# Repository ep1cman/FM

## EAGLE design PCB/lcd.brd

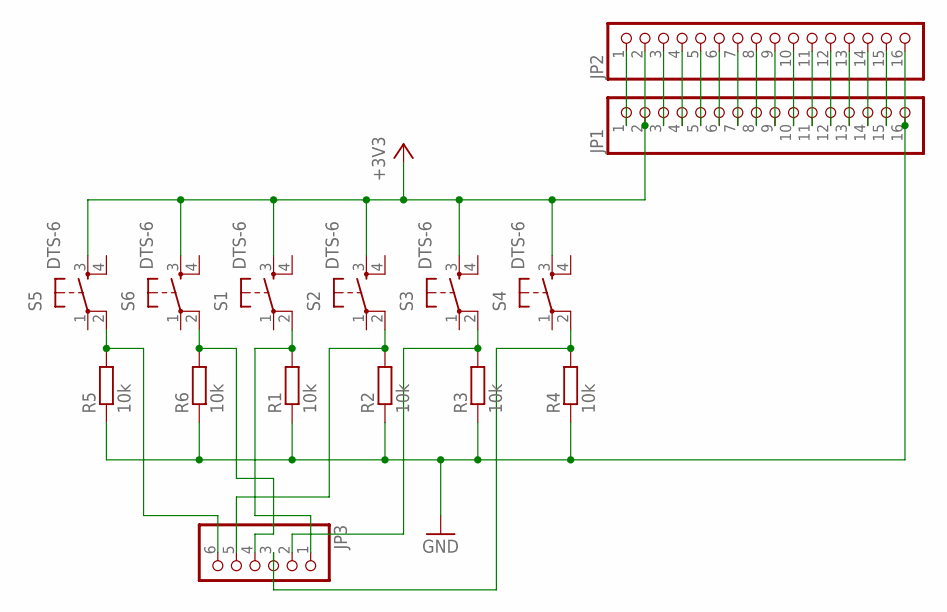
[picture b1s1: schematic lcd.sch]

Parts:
JP1, JP2: PINHD-1X16; 1X16
JP3: PINHD-1X6; 1X06
R1, R2, R3, R4, R5, R6: 10k; R0805
S1, S2, S3, S4, S5, S6: DTS-6

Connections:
+3V3: JP1.2, JP2.2, S1.3, S2.3, S3.3, S4.3, S5.3, S6.3
GND: JP1.16, JP2.16, R1.1, R2.1, R3.1, R4.1, R5.1, R6.1
unnamed: JP3.1, R1.2, S1.2
unnamed: JP3.5, R2.2, S2.2
unnamed: JP3.2, R3.2, S3.2
unnamed: JP1.1, JP2.1
unnamed: JP3.3, R4.2, S4.2
unnamed: JP3.6, R5.2, S5.2
unnamed: JP3.4, R6.2, S6.2
unnamed: JP1.3, JP2.3
unnamed: JP1.4, JP2.4
unnamed: JP1.5, JP2.5
unnamed: JP1.6, JP2.6
unnamed: JP1.7, JP2.7
unnamed: JP1.8, JP2.8
unnamed: JP1.9, JP2.9
unnamed: JP1.10, JP2.10
unnamed: JP1.11, JP2.11
unnamed: JP1.12, JP2.12
unnamed: JP1.13, JP2.13
unnamed: JP1.14, JP2.14
unnamed: JP1.15, JP2.15

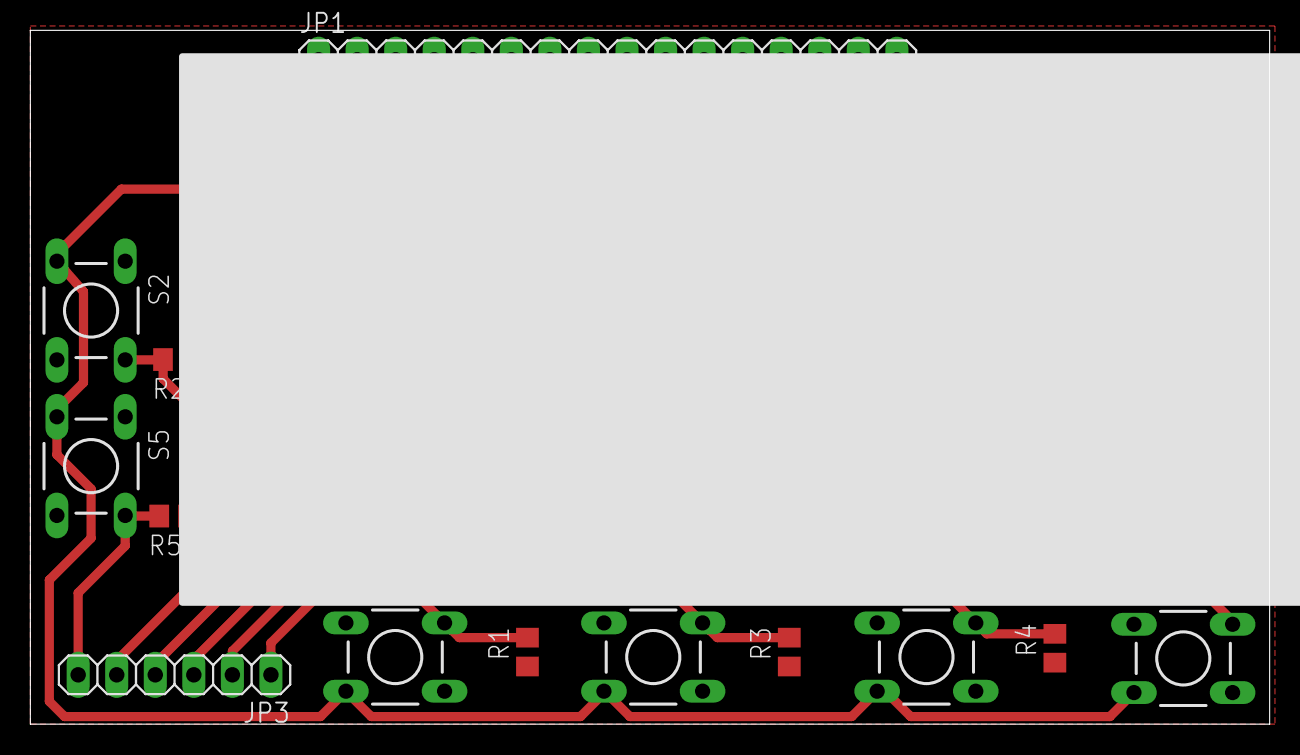
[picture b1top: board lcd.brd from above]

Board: 2 copper layers, 81.7 x 45.7 mm, 15 parts (0 on the bottom side), 22 nets.

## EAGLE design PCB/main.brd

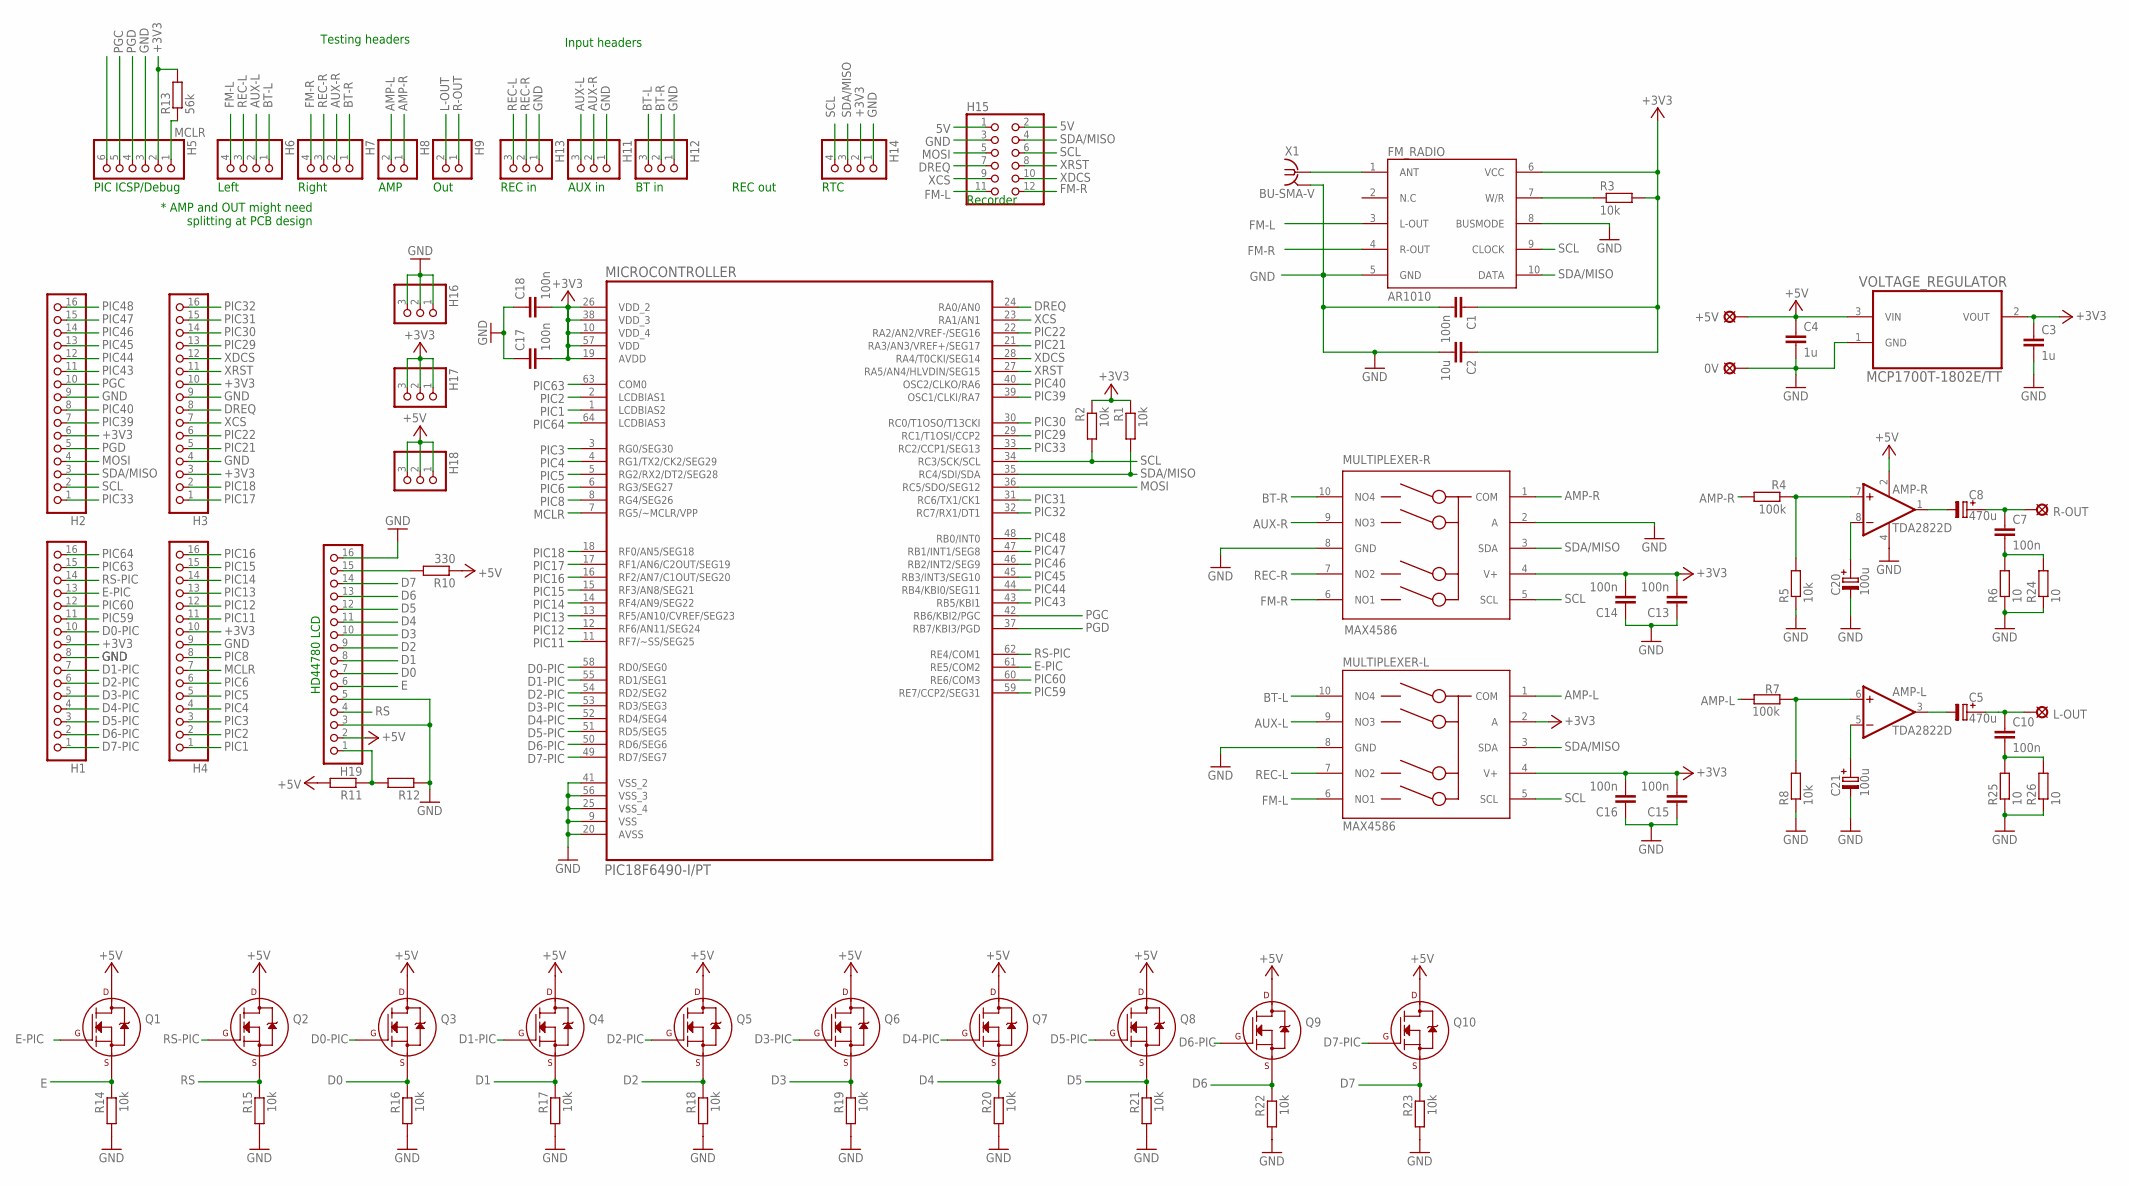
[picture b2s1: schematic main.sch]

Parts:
0V: LSP11
+5V: LSP11
AMP-: TDA2822D; SO08
C1, C7, C10, C13, C14, C15, C16, C17, C18: 100n; C0805
C2: 10u; C0805
C3, C4: 1u; C0805
C5, C8: 470u; SV-G
C20, C21: 100u; SV-D
H1, H2, H3, H4, H19: PINHD-1X16; 1X16
H5: PINHD-1X6; 1X06
H6, H7: PINHD-1X4; 1X04
H8, H9: PINHD-1X2; 1X02
H11, H12, H13, H16, H17, H18: PINHD-1X3; 1X03
H14: PINHD-1X4/90; 1X04/90
H15: PINHD-2X6; 2X06
L-OUT: LSP10
MICROCONTROLLER: PIC18F6490-I/PT; QFP50P1200X1200X120-64N
Q1, Q2, Q3, Q4, Q5, Q6, Q7, Q8, Q9, Q10: 2N7000_SOT23; SOT-23
R1, R2, R3, R5, R8, R14, R15, R16, R17, R18, R19, R20, R21, R22, R23: 10k; M0805
R4, R7: 100k; M0805
R6, R24, R25, R26: 10; M0805
R10: 330; M0805
R11, R12: R-EU_M0805; M0805
R13: 56k; M0805
R-OUT: LSP10
U$1, U$3: MAX4586; UMAX10
U$2: AR1010
VOLTAGE_REGULATOR: MCP1700T-1802E/TT; SOT95P237X112-3N
X1: BU-SMA-V

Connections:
5V: H15.1, H15.2
+3V3: C1.1, C2.1, C3.1, C13.2, C14.2, C15.2, C16.2, C17.2, C18.2, H1.9, H2.6, H3.3, H3.10, H4.10, H5.2, H14.2, H17.1, H17.2, H17.3, MICROCONTROLLER.10 (VDD_4), MICROCONTROLLER.19 (AVDD), MICROCONTROLLER.26 (VDD_2), MICROCONTROLLER.38 (VDD_3), MICROCONTROLLER.57 (VDD), R1.1, R2.1, R3.2, R13.2, U$1.4 (V+), U$2.6 (VCC), U$3.2 (A), U$3.4 (V+), VOLTAGE_REGULATOR.2 (VOUT)
+5V: +5V.MP, AMP-.2 (V+), C4.1, H18.1, H18.2, H18.3, H19.2, Q1.3 (D), Q2.3 (D), Q3.3 (D), Q4.3 (D), Q5.3 (D), Q6.3 (D), Q7.3 (D), Q8.3 (D), Q9.3 (D), Q10.3 (D), R10.1, R11.2, VOLTAGE_REGULATOR.3 (VIN)
AMP-L: H8.2, R7.1, U$3.1 (COM)
AMP-R: H8.1, R4.2, U$1.1 (COM)
AUX-L: H6.2, H11.3, U$3.9 (NO3)
AUX-R: H7.2, H11.2, U$1.9 (NO3)
BT-L: H6.1, H12.3, U$3.10 (NO4)
BT-R: H7.1, H12.2, U$1.10 (NO4)
D0: H19.7, Q3.2 (S), R16.1
D0-PIC: H1.10, MICROCONTROLLER.58 (RD0/SEG0), Q3.1 (G)
D1: H19.8, Q4.2 (S), R17.1
D1-PIC: H1.7, MICROCONTROLLER.55 (RD1/SEG1), Q4.1 (G)
D2: H19.9, Q5.2 (S), R18.1
D2-PIC: H1.6, MICROCONTROLLER.54 (RD2/SEG2), Q5.1 (G)
D3: H19.10, Q6.2 (S), R19.1
D3-PIC: H1.5, MICROCONTROLLER.53 (RD3/SEG3), Q6.1 (G)
D4: H19.11, Q7.2 (S), R20.1
D4-PIC: H1.4, MICROCONTROLLER.52 (RD4/SEG4), Q7.1 (G)
D5: H19.12, Q8.2 (S), R21.1
D5-PIC: H1.3, MICROCONTROLLER.51 (RD5/SEG5), Q8.1 (G)
D6: H19.13, Q9.2 (S), R22.1
D6-PIC: H1.2, MICROCONTROLLER.50 (RD6/SEG6), Q9.1 (G)
D7: H19.14, Q10.2 (S), R23.1
D7-PIC: H1.1, MICROCONTROLLER.49 (RD7/SEG7), Q10.1 (G)
DREQ: H3.8, H15.7, MICROCONTROLLER.24 (RA0/AN0)
E: H19.6, Q1.2 (S), R14.1
E-PIC: H1.13, MICROCONTROLLER.61 (RE5/COM2), Q1.1 (G)
FM-L: H6.4, H15.11, U$2.3 (L-OUT), U$3.6 (NO1)
FM-R: H7.4, H15.12, U$1.6 (NO1), U$2.4 (R-OUT)
GND: 0V.MP, AMP-.4 (V-), C1.2, C2.2, C3.2, C4.2, C13.1, C14.1, C15.1, C16.1, C17.1, C18.1, C20.-, C21.-, H1.8, H2.9, H3.4, H3.9, H4.9, H5.3, H11.1, H12.1, H13.1, H14.1, H15.3, H16.1, H16.2, H16.3, H19.3, H19.5, H19.16, MICROCONTROLLER.9 (VSS), MICROCONTROLLER.20 (AVSS), MICROCONTROLLER.25 (VSS_4), MICROCONTROLLER.41 (VSS_2), MICROCONTROLLER.56 (VSS_3), R5.1, R6.1, R8.1, R12.1, R14.2, R15.2, R16.2, R17.2, R18.2, R19.2, R20.2, R21.2, R22.2, R23.2, R24.1, R25.1, R26.1, U$1.2 (A), U$1.8 (GND), U$2.5 (GND), U$2.8 (BUSMODE), U$3.8 (GND), VOLTAGE_REGULATOR.1 (GND), X1.2, X1.3 (2), X1.4 (2), X1.5 (2)
L-OUT: C5.+, C10.1, H9.2, L-OUT.MP
MCLR: H4.7, H5.1, MICROCONTROLLER.7 (RG5/~MCLR/VPP), R13.1
MOSI: H2.4, H15.5, MICROCONTROLLER.36 (RC5/SDO/SEG12)
unnamed: AMP-.8 (-IN), C20.+
unnamed: R3.1, U$2.7 (W/R)
unnamed: U$2.1 (ANT), X1.1
unnamed: AMP-.3 (OUT), C5.-
unnamed: AMP-.1 (OUT), C8.-
unnamed: AMP-.7 (+IN), R4.1, R5.2
unnamed: C10.2, R25.2, R26.2
unnamed: H19.1, R11.1, R12.2
unnamed: AMP-.5 (-IN), C21.+
unnamed: AMP-.6 (+IN), R7.2, R8.2
unnamed: H19.15, R10.2
unnamed: C7.2, R6.2, R24.2
PGC: H2.10, H5.5, MICROCONTROLLER.42 (RB6/KBI2/PGC)
PGD: H2.5, H5.4, MICROCONTROLLER.37 (RB7/KBI3/PGD)
PIC1: H4.1, MICROCONTROLLER.1 (LCDBIAS2)
PIC2: H4.2, MICROCONTROLLER.2 (LCDBIAS1)
PIC3: H4.3, MICROCONTROLLER.3 (RG0/SEG30)
PIC4: H4.4, MICROCONTROLLER.4 (RG1/TX2/CK2/SEG29)
PIC5: H4.5, MICROCONTROLLER.5 (RG2/RX2/DT2/SEG28)
PIC6: H4.6, MICROCONTROLLER.6 (RG3/SEG27)
PIC8: H4.8, MICROCONTROLLER.8 (RG4/SEG26)
PIC11: H4.11, MICROCONTROLLER.11 (RF7/~SS/SEG25)
PIC12: H4.12, MICROCONTROLLER.12 (RF6/AN11/SEG24)
PIC13: H4.13, MICROCONTROLLER.13 (RF5/AN10/CVREF/SEG23)
PIC14: H4.14, MICROCONTROLLER.14 (RF4/AN9/SEG22)
PIC15: H4.15, MICROCONTROLLER.15 (RF3/AN8/SEG21)
PIC16: H4.16, MICROCONTROLLER.16 (RF2/AN7/C1OUT/SEG20)
PIC17: H3.1, MICROCONTROLLER.17 (RF1/AN6/C2OUT/SEG19)
PIC18: H3.2, MICROCONTROLLER.18 (RF0/AN5/SEG18)
PIC21: H3.5, MICROCONTROLLER.21 (RA3/AN3/VREF+/SEG17)
PIC22: H3.6, MICROCONTROLLER.22 (RA2/AN2/VREF-/SEG16)
PIC29: H3.13, MICROCONTROLLER.29 (RC1/T1OSI/CCP2)
PIC30: H3.14, MICROCONTROLLER.30 (RC0/T1OSO/T13CKI)
PIC31: H3.15, MICROCONTROLLER.31 (RC6/TX1/CK1)
PIC32: H3.16, MICROCONTROLLER.32 (RC7/RX1/DT1)
PIC33: H2.1, MICROCONTROLLER.33 (RC2/CCP1/SEG13)
PIC39: H2.7, MICROCONTROLLER.39 (OSC1/CLKI/RA7)
PIC40: H2.8, MICROCONTROLLER.40 (OSC2/CLKO/RA6)
PIC43: H2.11, MICROCONTROLLER.43 (RB5/KBI1)
PIC44: H2.12, MICROCONTROLLER.44 (RB4/KBI0/SEG11)
PIC45: H2.13, MICROCONTROLLER.45 (RB3/INT3/SEG10)
PIC46: H2.14, MICROCONTROLLER.46 (RB2/INT2/SEG9)
PIC47: H2.15, MICROCONTROLLER.47 (RB1/INT1/SEG8)
PIC48: H2.16, MICROCONTROLLER.48 (RB0/INT0)
PIC59: H1.11, MICROCONTROLLER.59 (RE7/CCP2/SEG31)
PIC60: H1.12, MICROCONTROLLER.60 (RE6/COM3)
PIC63: H1.15, MICROCONTROLLER.63 (COM0)
PIC64: H1.16, MICROCONTROLLER.64 (LCDBIAS3)
R-OUT: C7.1, C8.+, H9.1, R-OUT.MP
REC-L: H6.3, H13.3, U$3.7 (NO2)
REC-R: H7.3, H13.2, U$1.7 (NO2)
RS: H19.4, Q2.2 (S), R15.1
RS-PIC: H1.14, MICROCONTROLLER.62 (RE4/COM1), Q2.1 (G)
SCL: H2.2, H14.4, H15.6, MICROCONTROLLER.34 (RC3/SCK/SCL), R2.2, U$1.5 (SCL), U$2.9 (CLOCK), U$3.5 (SCL)
SDA/MISO: H2.3, H14.3, H15.4, MICROCONTROLLER.35 (RC4/SDI/SDA), R1.2, U$1.3 (SDA), U$2.10 (DATA), U$3.3 (SDA)
XCS: H3.7, H15.9, MICROCONTROLLER.23 (RA1/AN1)
XDCS: H3.12, H15.10, MICROCONTROLLER.28 (RA4/T0CKI/SEG14)
XRST: H3.11, H15.8, MICROCONTROLLER.27 (RA5/AN4/HLVDIN/SEG15)

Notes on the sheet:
PIC ICSP/Debug
HD44780 LCD
AMP
Out
Left
Right
Testing headers
Input headers
* AMP and OUT might need splitting at PCB design
REC out
REC in
AUX in
Recorder
RTC
BT in

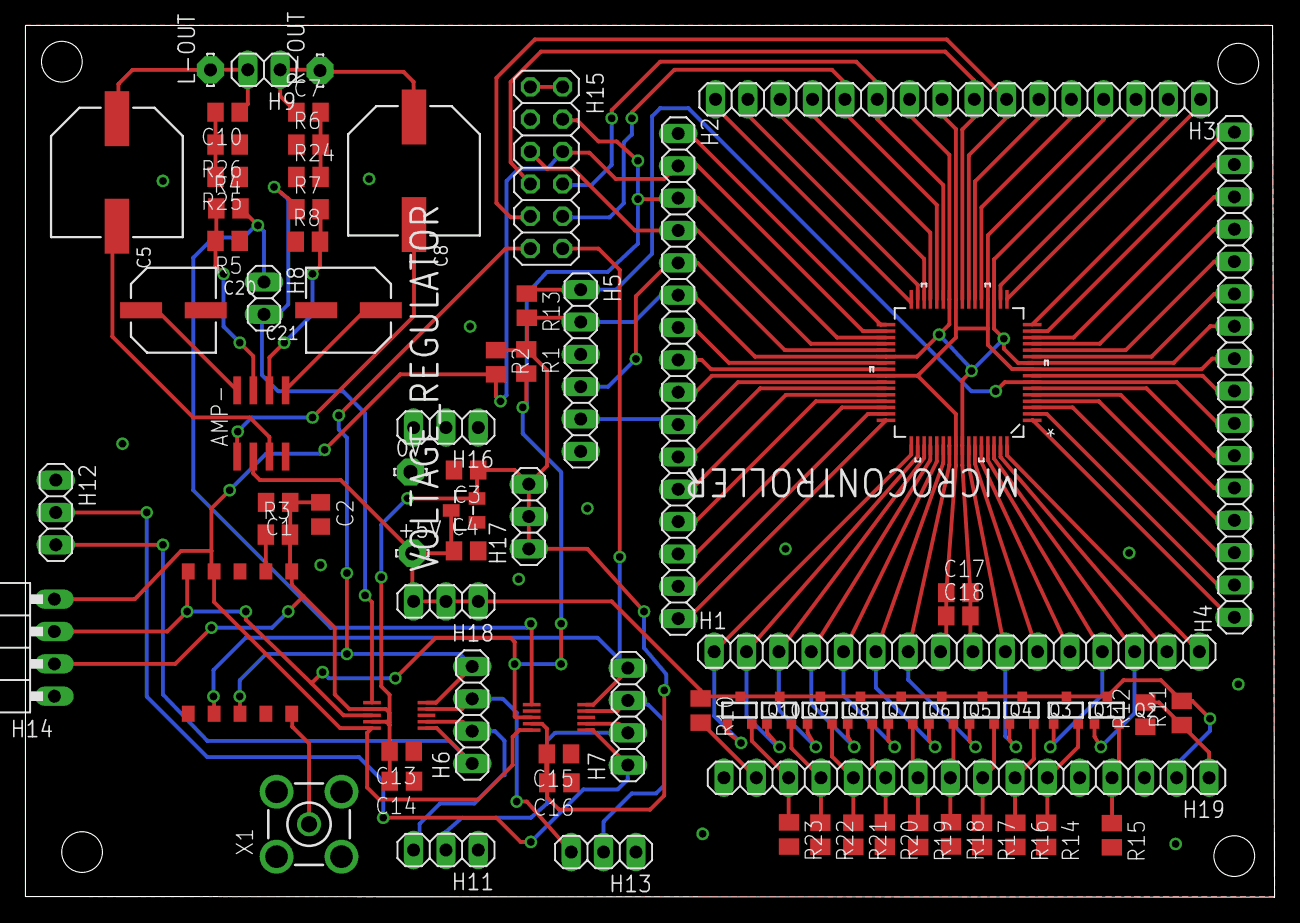
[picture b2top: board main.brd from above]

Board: 2 copper layers, 98.1 x 68.5 mm, 80 parts (0 on the bottom side), 92 nets.

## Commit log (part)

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2015-02-08 Datasheets + Lab manual
    Got datasheets for:
    - PIC18LF6490
    - TDA7050
    - AR1010 (Programming manual)
    - PIC I2C master
    Also made a PDF of the relevant lab manual section
2015-02-09 Added Labs provided datasheet.
2015-02-09 Week 1 time plan
    - Created time plan folder
    - Added simple time plan for week 1
2015-02-09 Labs documentation webpage.
2015-02-09 Updated Week 1 time plan
    - Added more detail to Phil's time plan
2015-02-10 Audio Amplifier
    Figure on first page is circuit used.
2015-02-11 Added datasheets
    - Removed incorrect amplifier datasheet
    - Added LCD datasheet
    - Added LCD breakout board documentation
2015-02-11 Created MPLAB project
    Added skeleton MPLAB project
2015-02-12 Add VS1053 audio processor chip datasheet.
2015-02-12 Added discussion notes
    - Created a discussions and observations folder
    - Saved notes from a conversation between seb and phil on 11/02/2015
2015-02-13 General Timeplan
2015-02-16 Added meeting minutes.
2015-02-16 Week 2 time plan
    - Added time plan for week 2
2015-02-16 Tidied up datasheets
2015-02-16 Removed extra week 1 file
2015-02-16 PCB Libraries + AR1010 breakout spec sheet
    - Added libraries for PIC18F6490 (from element14)
    - Added spec sheet for TFM-10101 board
    - Added custom made AR1010 library
2015-02-17 Created initial software flowchart.
2015-02-18 Created polling debounce function
    - Added MPLAB project for the debug express board
    - Created a polling debug function
    - Added labs observations
2015-02-18 Fixed file extension
2015-02-18 Added AR1010 breakout board pics.
2015-02-18 Initial EAGLE schematic entry
    - AR1010
    - Start of PIC
2015-02-18 Continued schematic work
    Finished PIC ICSP header, added intial LCD header.
2015-02-18 More schematic.
    Added complete PIC breakout headers.
2015-02-18 Yet more schematic.
    Added voltage regulator.
2015-02-18 Yet even more schematic.
2015-02-18 AMP eagle part
2015-02-19 Eagle Schematic Layout Changes
2015-02-20 Schematic work
    - Added MAX4586 part
    - Schematic work
2015-02-20 Revert "Merge branch 'master' of https://github.com/ep1cman/FM"
    This reverts commit c620d54a34bc759afa39deca24740301f1b7634a, reversing
    changes made to 421763858366320255c2fd29161aed01bdffe800.
    Fixed EAGLE merge screw up
2015-02-20 Eagle Schematic From Lab
2015-02-20 Eagle Schematic Changes
    Pins numbers added
    IC names added
    Text re-aligned
    Amp corrected
    Components re-named
2015-02-20 Eagle Schematic Changes
    Fixed a few issues that didn't save properly.
2015-02-20 Eagle Schematic Changes
    - Added V+, 3.3v and GND pads
    - Split off ISCP, I2C and AUX connectors
    - Various visual changes
    - Added pull up resistor for MCLR
2015-02-21 Eagle Schematic Changes
    - Rearranged PIC pin breakout headers.
    - Added REC-in pin header.
2015-02-21 Eagle Schematic Changes
    - Split off FM out connector
2015-02-21 Eagle Schematic Changes
    Test pins added
    Recorder pins added
2015-02-22 Eagle Schematic Changes
    - Altered headers
    - Replaced solder pads with pin headers
    - Connected rec pins
    - Added RTC
    - Swapped V+ for 5V connections
    - Swapped amplifier to 5v supply
2015-02-22 Datasheet
    Added data sheet for SN74LVCC3245A 5v to 3v3 logic buffer
2015-02-22 gitignore update
    Added office temp files to .gitignore
2015-02-22 Eagle Schematic Changes
    Added BT to left and right test headers
2015-02-22 Eagle Part Library
    Added the element 14 TI parts library containing the SN74LVCC3245A
    (logic buffer)
2015-02-22 Eagle Schematic Changes
    Simple layout and naming changes
2015-02-23 Eagle Part Library
    Added transistor part library for SOT-23-3 MOSFET
2015-02-23 Eagle Schematic Changes
    Added level shifters
2015-02-24 Week 3 time plan
    Added week 3 time plan:
    - Stuart LCD
    - Phil MIA
    - Seb Radio
2015-02-24 AR1010 I2C commands for initialisation, seek, tune, volume. Tested and verified working during week 3 lab session!
2015-02-24 Folder Organisation
2015-02-24 MPLAB Project template
    - Returned the FM.X project to the root
    - Other project to be put into branches and deleted
2015-02-24 LCD code moved to branch
2015-02-24 Removed old LCD data sheet
2015-02-25 Fix PIC oscillator setting
    - Changed PIC to used internal oscillator
    - Defined the clock speed for use in delay functions
2015-02-25 Tune Radio
    Added functions to:
    - Write registers
    - Read registers
    - Set/Clear bits in a register
    - Initialise AR1010
    - Tune to a given frequency in MHz
2015-02-25 MPLAB gitignore
2015-02-25 MPLAB gitignore cont.
    Continues MPLAB tidy up & gitignore
2015-02-25 Labs notes
    Added notes from the week 3 lab
2015-02-25 Order invoices
    - Added Order invoice folder
    - Added eBay and Onecall invoices
2015-02-25 Fixed/Completed tune function
    - Fixed setting CHAN value
    - Implemented wait for STC flag
2015-02-25 Soft mute disable
    Changed default state of soft mute to disabled
2015-02-25 Read register update
    Made readRegister() save the read value if it is in a register we are
    storing in memory
2015-02-25 Added Volume control
    Created functions to control volume of the AR1010
2015-02-25 Panasonic SMD capacitors eagle library.
2015-02-25 Initial PCB layout
    ~75% complete.
2015-02-26 Added i2c.h import and hmute and smute functions
2015-02-26 gitignore
    Added thumbs.db to gitignore (windows picture thumbnails)
2015-03-02 gitignore & eagle tidy up
    Since git already provides us with a way to revert eagle changes:
    - Removed eagle backup files
    - Added eagle backup files to gitignore
2015-03-03 LCD Main Code
    Data for output still in need of loading, once ROM code number obtained.
2015-03-03 LCD Code - pointers removed
2015-03-03 LCD Code
    - Data Added
    - Loop Changed
    - Variables Moved
2015-03-03 LCD pinout
2015-03-03 LCD Code
    - major rework of code
    - Write functions for instructions and data complete
    - Initialisation functions complete
    - Minor functions added for simplicity
    - Delay function added
    - Data select function added
2015-03-04 LCD Code
    -Empty line removed
2015-03-08 Week 3 time plan
    Seb: Implementing and testing radio
    Stuart: Implementing LCD
    Phil: PCB stencil testing
2015-03-08 Updated time plan
    - Added keypad task for myself
    - Added deliverables
2015-03-08 Gnatt Chart review
    Listed completed, removed and slipped tasks
2015-03-08 Colour Correction
2015-03-08 PCB + Schematic
    - E-Pic issue fixed
2015-03-08 Dimensions for front panel design.
2015-03-08 PCB Layout
    - Reworked the whole board to shrink it significantly
    - Added DRC check file
    - Fixed BT audio net name
2015-03-08 PCB stencil test observations.
2015-03-08 PCB Layout
    -Track widths fixed
    -Routing through headers neatened
2015-03-08 PCB Schematic Change
    5V Supply Pad was not connected to 5V net
2015-03-08 PCB Layout
    -All connections should be complete
2015-03-08 PCB Layout
    - DRC performed (all clearance settings 6mil)
2015-03-08 PCB Layout
    -Tracks at bottom of pic made symmetrical
2015-03-08 Datasheet added
    - Added the datasheet for the MAX4587 Audio multiplexer
2015-03-08 "Final" PCB changes
    Changes from group PCB review
2015-03-08 PCB
    -Junction added to E net
2015-03-08 REALLY FINAL PCB changes!
    Made mounting hole location consistent.
    Changed PICkit silkscreen layer.
2015-03-08 FINAL! PCB changes
    - Keep out for ground plane inside PIC fanout
    - Connected ground vias to ground net
2015-03-08 Updated Deliverables
    Colourised deliverables:
    RED - Failed
    YELLOW - Done but not in labs
    GREEN - Done
2015-03-09 Week 5 time plan.
2015-03-09 Updated time plan.
2015-03-09 Initial front panel layout for laser cutting.
2015-03-10 FIxed MPLAB Bug
    Fixed an issue caused by a bug in MPLAB that means arrays on unsigned chars cannot be made without causing corruption while making the hex file
2015-03-10 Corrected AR1010 initialisation
    The AR1010 needs register 0 to be skipped and written to last.
    Also adjusted default value to match datasheet
2015-03-10 Fixed volume and tune functions
    Changed the chan formula in the tune function to avoid integer rounding
    Moved volume limit checks to setVolume
    Fixed shift mistake in setVolume
2015-03-10 Tuned AR1010 into Eagle FM
2015-03-10 / ‘README.md’
2015-03-12 LCD Code
    - Initialisation
    - Write command/data
    - set cursor location
    - print strings
2015-03-23 Added RTC datasheet
    Added datasheet for the Maxim DS3231 Real Time Clock (RTC)
2015-03-23 Removed soft mute functions
    Removed the soft mute functions because they didnt seem to work and the
    hardware mute ones did making these pointless
2015-03-23 Added seek function
    Added a function to allow seeking of a station
2015-03-23 Added getFrequency function
    - Added a function to read the frequency the AR1010 is currently tuned
    to
    - Changed the signature of the tune function to make it compatible with
    the output of getFrequency
2015-03-23 Added standby functions
    Added function allow the AR1010 to go in and out of standby
2015-03-23 Changed all setBit calls to use defines
    To improve readability all setBit calls had their register and bit
    parameters replaced with defines
2015-03-23 Moved AR1010 functions out of main.c
    - Made the AR1010 a library.
    - Fixed setVolume paramater to unsigned char
2015-03-23 Renamed readRegister
    Renamed readRegister to AR1010ReadRegister to avoid clashes with DS3231 functions
    This should likely be done to all AR1010 functions.
2015-03-23 Added DS3231 library
    Created functions to read the date and time (in 12h format) from the Maxim DS3231
2015-03-24 Schematic PDF
    Saved eagle schematic as a PDF for easier viewing
2015-03-24 Debounce code
    Added timer interrupt based debounce function
2015-03-24 DS3231 Fixes
    - Fixed BCD to decimal function
    - Fixed register read with nack and restart
    - Masked out century bit in month
    - Fixed hour reading
2015-03-24 Print date and time to LCD
2015-03-24 Moved LCD functions
    Moved the LCD functions into their own file.
2015-04-24 MAX4586 Mux Library
    Added library for the MAX4586 mux chips.
2015-04-25 AR1010 Fixes
    - Fixed incorrect merging of two bytes
    - Fixed Nack and Ack on reads
    - Volume underflow correction
2015-04-25 Added EEPROM chip datasheet.
2015-04-25 Draft test procedure
2015-04-25 Fixed debounce routine
    Fixed the debounce function and moved it over to PORTB.
2015-04-25 Lowered clock speed to 1Mhz
    I2C stopped working at 8MHz lowering the clock speed to 1MHz fixed it.
2015-04-25 FM Tuning menu
    Currently missing seek and presets do nothing.
2015-04-25 Simplified Mux library
    Removed the switch case and error output
2015-04-25 Added 24CN32 EEPROM chip library.
2015-04-25 AR1010 Fixes
    Fixed seek
    Volume functions clear mutes
2015-04-25 Seek and bluetooth
    Added a bluetooth menu
    Added seek to FM menu, rearanging the buttons
2015-04-25 MAX4586 Fixes
    Changed parameter to unsigned char
    Added files to project config file
2015-04-25 MAX4586 Fix
    updated header to match c file (forgot to add it to previous commit)
2015-04-26 Fixed EEPROM
    Added missing includes
2015-04-27 Initial library for VS1053 I2C recorder interface.
2015-04-27 Comment clarifications.
    Now what the library does might actually make sense. Stupid 3am.
2015-04-27 Front panel edits.
2015-04-29 Added a way to turn MUXs off
    Added the option to turn off all mux inputs if a valid channel was not selected
2015-04-29 LCD Custom characters
    Added custom characters to the LCD init:
    - Up & Down arrows
    - Bluetooth logo
    - Record circle
    - Tick
    Also added a command to turn blinking cursors on and off
2015-04-29 Fixed recorder library
    Phil should not code late at night...
2015-04-29 Menu
    Added the menu to select modes and all features. Mostly implemented the recorder features until the PIC ran out of memory
2015-05-17 Add Arduino recorder I2C slave code.
    Please don't judge me...
2015-05-17 Comments
    Tidied up and added a few comments

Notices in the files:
parts and their libraries:
cap-pan40: Copyright (C) 2004, Bob Starr
